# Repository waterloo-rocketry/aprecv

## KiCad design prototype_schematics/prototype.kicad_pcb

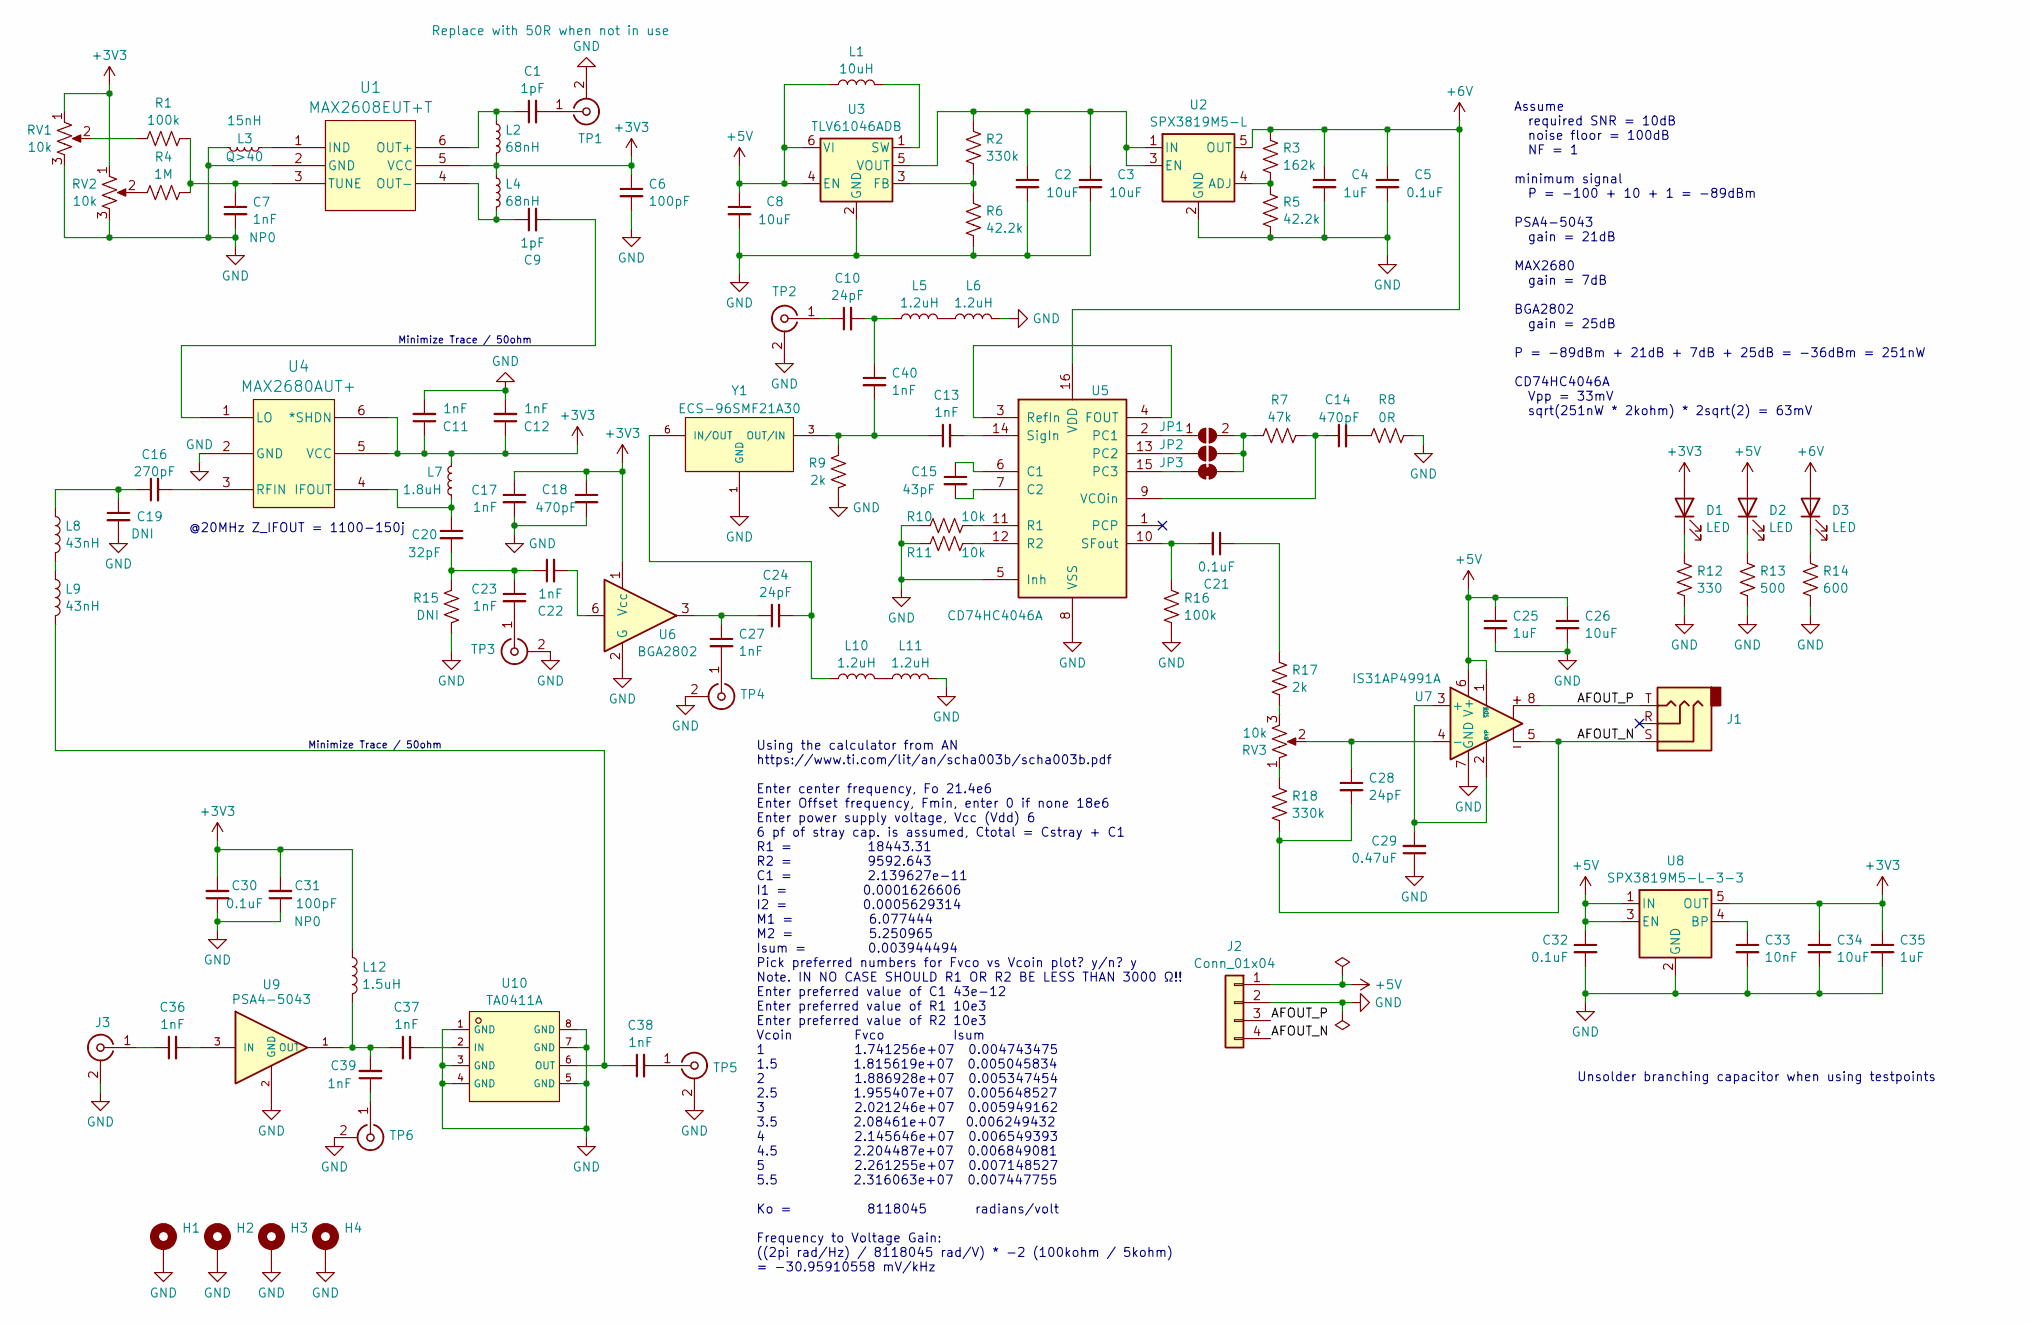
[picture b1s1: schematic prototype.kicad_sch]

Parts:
C1, C9: 1pF; C_0603_1608Metric_Pad1.08x0.95mm_HandSolder; Digikey 490-16342-1-ND
C2, C3, C8, C26, C34: 10uF; C_0805_2012Metric_Pad1.18x1.45mm_HandSolder
C4, C25, C35: 1uF; C_0805_2012Metric_Pad1.18x1.45mm_HandSolder
C5, C21, C30, C32: 0.1uF; C_0805_2012Metric_Pad1.18x1.45mm_HandSolder
C6, C31: 100pF; C_0603_1608Metric_Pad1.08x0.95mm_HandSolder; Digikey 720-1649-1-ND
C7, C11, C12, C13, C17, C22, C23, C27, C36, C37, C38, C39, C40: 1nF; C_0603_1608Metric_Pad1.08x0.95mm_HandSolder; Digikey 4713-GMC10CG102F50NTCT-ND
C10, C24, C28: 24pF; C_0603_1608Metric_Pad1.08x0.95mm_HandSolder; Digikey 13-CC0603FRNPO9BN240CT-ND
C14, C18: 470pF; C_0603_1608Metric_Pad1.08x0.95mm_HandSolder; Digikey 399-C0603C471F8HAC7867CT-ND
C15: 43pF; C_0603_1608Metric_Pad1.08x0.95mm_HandSolder; Digikey 490-GCM1885C2A430FA16DCT-ND
C16: 270pF; C_0603_1608Metric_Pad1.08x0.95mm_HandSolder; Digikey 490-16410-1-ND
C19: DNI; C_0603_1608Metric_Pad1.08x0.95mm_HandSolder
C20: 32pF; C_0603_1608Metric_Pad1.08x0.95mm_HandSolder; Digikey 478-06031A320FAT2ACT-ND
C29: 0.47uF; C_0805_2012Metric_Pad1.18x1.45mm_HandSolder; Digikey 1276-2082-1-ND
C33: 10nF; C_0805_2012Metric_Pad1.18x1.45mm_HandSolder; Digikey 490-4781-1-ND
D1, D2, D3: LED; LED_1206_3216Metric_Pad1.42x1.75mm_HandSolder
H1, H2, H3, H4: MountingHole_Pad; MountingHole_3.2mm_M3_Pad_TopBottom
J1: AudioJack3; CUI_SJ1-2503A; Digikey CP1-2503A-ND
J2: Conn_01x04; PinHeader_1x04_P2.54mm_Vertical
J3: Conn_Coaxial; SMA_Samtec_SMA-J-P-X-ST-EM1_EdgeMount; Digikey 931-1175-ND
JP1, JP3: SolderJumper_2_Open; SolderJumper-2_P1.3mm_Open_TrianglePad1.0x1.5mm
JP2: SolderJumper_2_Bridged; SolderJumper-2_P1.3mm_Open_TrianglePad1.0x1.5mm
L1: 10uH; L_0805_2012Metric_Pad1.15x1.40mm_HandSolder; Digikey 587-2045-1-ND
L2, L4: 68nH; L_0805_2012Metric_Pad1.15x1.40mm_HandSolder; Digikey 712-LRW0805WJ68NGG001ECT-ND
L3: 15nH; L_0603_1608Metric_Pad1.05x0.95mm_HandSolder; Digikey 490-1171-1-ND
L5, L6, L10, L11: 1.2uH; L_0805_2012Metric_Pad1.15x1.40mm_HandSolder; Digikey 2035-1186-1-ND
L7: 1.8uH; L_0805_2012Metric_Pad1.15x1.40mm_HandSolder; Digikey 445-MLF2012A1R8JT000CT-ND
L8, L9: 43nH; L_0603_1608Metric_Pad1.05x0.95mm_HandSolder; Digikey 490-6892-1-ND
L12: 1.5uH; L_0603_1608Metric_Pad1.05x0.95mm_HandSolder; Digikey 587-2898-1-ND
R1, R16: 100k; R_0805_2012Metric_Pad1.20x1.40mm_HandSolder
R2, R18: 330k; R_0805_2012Metric_Pad1.20x1.40mm_HandSolder; Digikey 311-330KCRCT-ND
R3: 162k; R_0805_2012Metric_Pad1.20x1.40mm_HandSolder; Digikey RMCF0805FT162KCT-ND
R4: 1M; R_0805_2012Metric_Pad1.20x1.40mm_HandSolder
R5, R6: 42.2k; R_0805_2012Metric_Pad1.20x1.40mm_HandSolder; Digikey 311-42.2KCRCT-ND
R7: 47k; R_0805_2012Metric_Pad1.20x1.40mm_HandSolder; Digikey 311-47.0KCRCT-ND
R8: 0R; R_0805_2012Metric_Pad1.20x1.40mm_HandSolder
R9, R17: 2k; R_0805_2012Metric_Pad1.20x1.40mm_HandSolder; Digikey RMCF0805FT2K00CT-ND
R10, R11: 10k; R_0805_2012Metric_Pad1.20x1.40mm_HandSolder
R12: 330; R_0805_2012Metric_Pad1.20x1.40mm_HandSolder
R13: 500; R_0805_2012Metric_Pad1.20x1.40mm_HandSolder
R14: 600; R_0805_2012Metric_Pad1.20x1.40mm_HandSolder
R15: DNI; R_0805_2012Metric_Pad1.20x1.40mm_HandSolder
RV1, RV2, RV3: 10k; TRIM_PT01-D120K2-B103; Digikey 2223-PT01-B120D-B103-ND
TP1, TP2, TP3, TP4, TP5, TP6: Conn_Coaxial; U.FL_Molex_MCRF_73412-0110_Vertical; Digikey 343-CONMHF1-SMD-TCT-ND
U1: MAX2608EUT+T; 21-0058I_MXM; Digikey MAX2608EUT+TCT-ND
U2: SPX3819M5-L; SOT-23-5; Digikey 1016-1871-1-ND
U3: TLV61046ADB; SOT-23-6; Digikey 296-47674-1-ND
U4: MAX2680AUT+; 21-0058I_MXM; Digikey 175-MAX2680AUT+TCT-ND
U5: CD74HC4046A; SOIC-16_3.9x9.9mm_P1.27mm; Digikey 296-9209-5-ND
U6: BGA2802; SOT-363_SC-70-6_Handsoldering; Digikey 568-14547-1-ND
U7: IS31AP4991A; SOP-8_3.76x4.96mm_P1.27mm; Digikey 2521-IS31AP4991A-GRLS2-TRCT-ND
U8: SPX3819M5-L-3-3; SOT-23-5; Digikey 1016-1873-1-ND
U9: PSA4-5043; Digikey 3157-PSA4-5043+CT-ND
U10: TA0411A; FILTER-SMD_8P-L5.0-W5.0-BL; LCSC C692400
Y1: ECS-96SMF21A30; XTAL_ECS-96SMF21A30; Digikey X717CT-ND

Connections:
+3V3: C6.1, C11.1, C12.1, C17.1, C18.1, C30.2, C31.2, C34.1, C35.1, D1.2 (A), L2.2, L4.1, L7.1, L12.1, RV1.1, RV2.1, U1.5 (VCC), U4.5 (VCC), U4.6 (*SHDN), U6.1 (Vcc), U8.5 (OUT)
+5V: C8.1, C25.1, C26.1, C32.1, D2.2 (A), J2.1, L1.1, U3.4 (EN), U3.6 (VI), U7.1 (~SDB), U7.6 (V+), U8.1 (IN), U8.3 (EN)
+6V: C4.1, C5.1, D3.2 (A), R3.1, U2.5 (OUT), U5.16 (VDD)
/AFOUT_N: C28.2, J1.S, J2.4, R18.2, U7.5
/AFOUT_P: J1.T, J2.3, U7.8
GND: C2.2, C3.2, C4.2, C5.2, C6.2, C7.2, C8.2, C11.2, C12.2, C17.2, C18.2, C19.2, C25.2, C26.2, C29.1, C30.1, C31.1, C32.2, C33.2, C34.2, C35.2, H1.1, H2.1, H3.1, H4.1, J2.2, J3.2 (Ext), L3.2, L6.2, L11.2, R5.2, R6.2, R8.2, R9.2, R10.1, R11.1, R12.2, R13.2, R14.2, R15.2, R16.2, RV1.3, RV2.3, TP1.2 (Ext), TP2.2 (Ext), TP3.2 (Ext), TP4.2 (Ext), TP5.2 (Ext), TP6.2 (Ext), U1.2 (GND), U2.2 (GND), U3.2 (GND), U4.2 (GND), U5.5 (Inh), U5.8 (VSS), U6.2 (G), U6.4 (G), U6.5 (G), U7.7 (GND), U8.2 (GND), U9.2 (GND), U9.4 (GND), U10.1 (GND), U10.3 (GND), U10.4 (GND), U10.5 (GND), U10.7 (GND), U10.8 (GND), Y1.1 (GND), Y1.2 (GND), Y1.4 (GND), Y1.5 (GND)
unnamed: C10.2, C40.1, L5.1
unnamed: C14.2, R8.1
unnamed: C16.1, C19.1, L8.1
unnamed: C20.2, C22.1, C23.1, R15.1
unnamed: C21.1, R17.1
unnamed: C22.2, U6.6
unnamed: C24.1, C27.1, U6.3
unnamed: D1.1 (K), R12.1
unnamed: D2.1 (K), R13.1
unnamed: D3.1 (K), R14.1
unnamed: C36.1, J3.1 (In)
unnamed: JP1.1 (A), U5.2 (PC1)
unnamed: JP1.2 (B), JP2.2 (B), JP3.2 (B), R7.1
unnamed: JP2.1 (A), U5.13 (PC2)
unnamed: JP3.1 (A), U5.15 (PC3)
unnamed: L5.2, L6.1
unnamed: L8.2, L9.1
unnamed: L10.2, L11.1
unnamed: R1.1, RV1.2
unnamed: R4.1, RV2.2
unnamed: R17.2, RV3.3
unnamed: R18.1, RV3.1
unnamed: C1.2, TP1.1 (In)
unnamed: C10.1, TP2.1 (In)
unnamed: C23.2, TP3.1 (In)
unnamed: C27.2, TP4.1 (In)
unnamed: C38.2, TP5.1 (In)
unnamed: C39.1, TP6.1 (In)
unnamed: L3.1, U1.1 (IND)
unnamed: C1.1, L2.1, U1.6 (OUT+)
unnamed: C9.1, L4.2, U1.4 (OUT-)
unnamed: C7.1, R1.2, R4.2, U1.3 (TUNE)
unnamed: R3.2, R5.1, U2.4 (ADJ)
unnamed: C2.1, C3.1, R2.1, U2.1 (IN), U2.3 (EN), U3.5 (VOUT)
unnamed: R2.2, R6.1, U3.3 (FB)
unnamed: L1.2, U3.1 (SW)
unnamed: C20.1, L7.2, U4.4 (IFOUT)
unnamed: C9.2, U4.1 (LO)
unnamed: C16.2, U4.3 (RFIN)
unnamed: C15.1, U5.6 (C1)
unnamed: C15.2, U5.7 (C2)
unnamed: U5.3 (RefIn), U5.4 (FOUT)
unnamed: R10.2, U5.11 (R1)
unnamed: R11.2, U5.12 (R2)
unnamed: C21.2, R16.1, U5.10 (SFout)
unnamed: C13.2, U5.14 (SigIn)
unnamed: C14.1, R7.2, U5.9 (VCOin)
unnamed: C29.2, U7.2 (BYP), U7.3 (+)
unnamed: C28.1, RV3.2, U7.4 (-)
unnamed: C33.1, U8.4 (BP)
unnamed: C36.2, U9.3 (IN)
unnamed: C37.1, C39.2, L12.2, U9.1 (OUT)
unnamed: C37.2, U10.2 (IN)
unnamed: C38.1, L9.2, U10.6 (OUT)
unnamed: C24.2, L10.1, Y1.6 (IN/OUT)
unnamed: C13.1, C40.2, R9.1, Y1.3 (OUT/IN)

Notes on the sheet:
Using the calculator from AN https://www.ti.com/lit/an/scha003b/scha003b.pdf Enter center frequency, Fo 21.4e6 Enter Offset frequency, Fmin, enter 0 if none 18e6 Enter power supply voltage, Vcc (Vdd) 6 6 pf of stray cap. is assumed, Ctotal = Cstray + C1 R1 = 18443.31 R2 = 9592.643 C1 = 2.139627e-11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
Unsolder branching capacitor when using testpoints
Assume required SNR = 10dB noise floor = 100dB NF = 1 minimum signal P = -100 + 10 + 1 = -89dBm PSA4-5043 gain = 21dB MAX2680 gain = 7dB BGA2802 gain = 25dB P = -89dBm + 21dB + 7dB + 25dB = -36dBm = 251nW CD74HC4046A Vpp = 33mV sqrt(251nW * 2kohm) * 2sqrt(2) = 63mV
Minimize Trace / 50ohm
@20MHz Z_IFOUT = 1100-150j

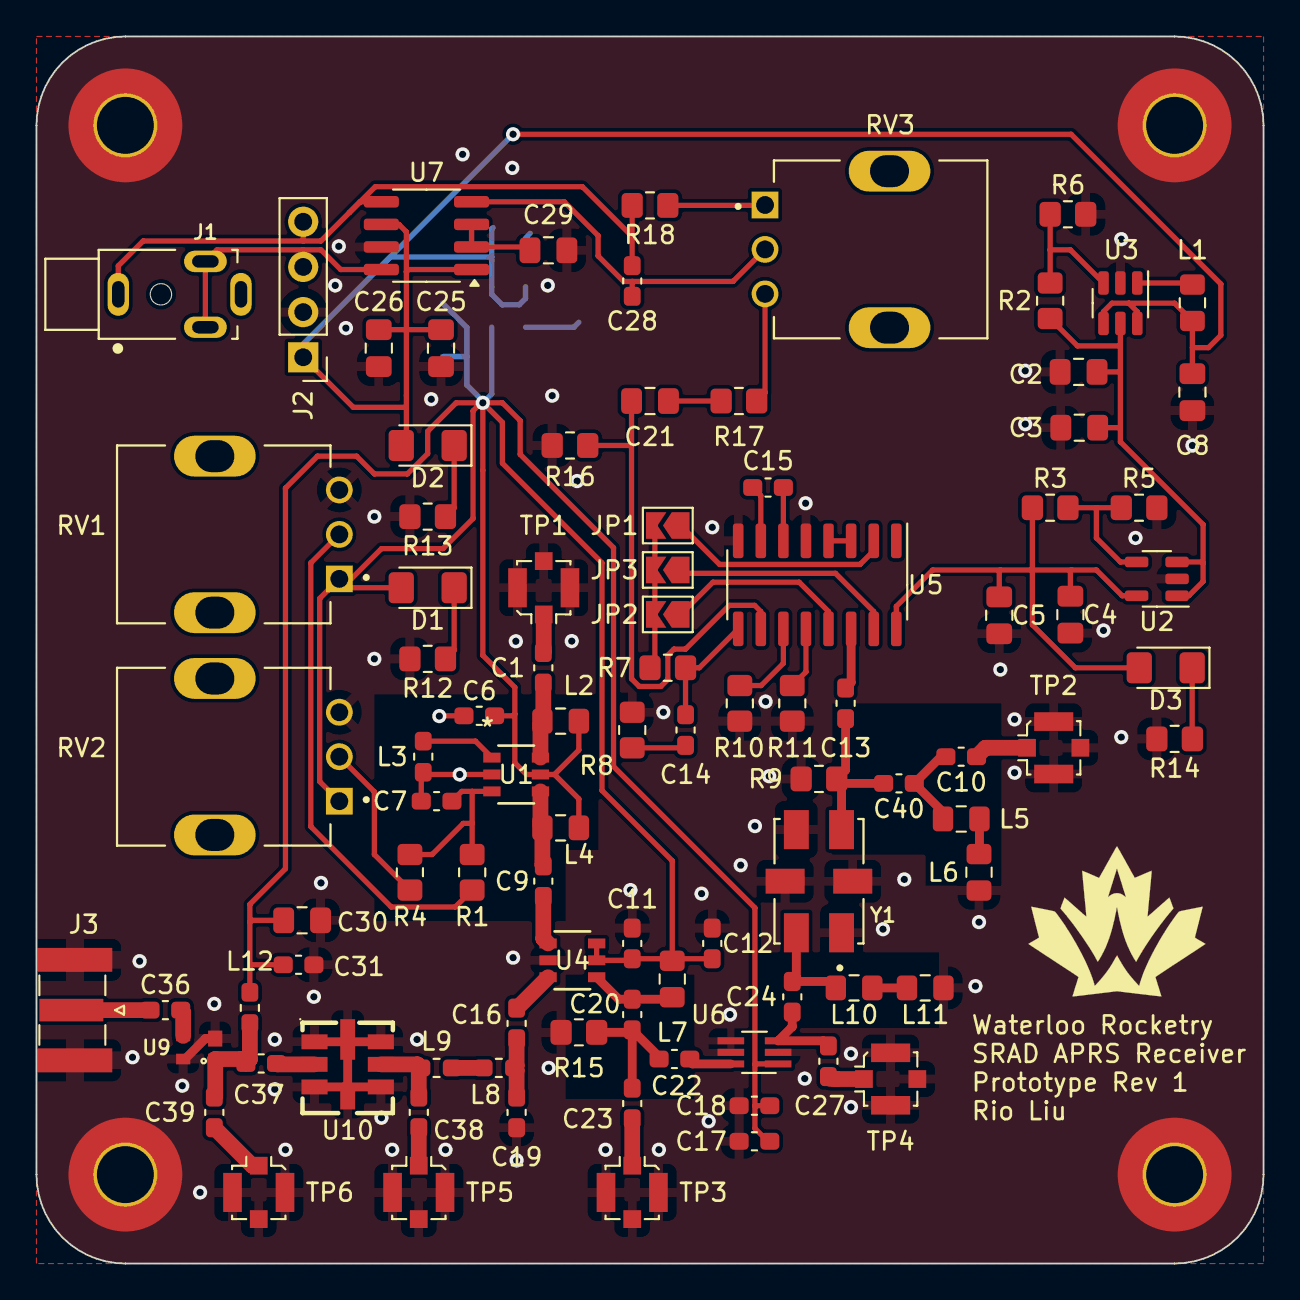
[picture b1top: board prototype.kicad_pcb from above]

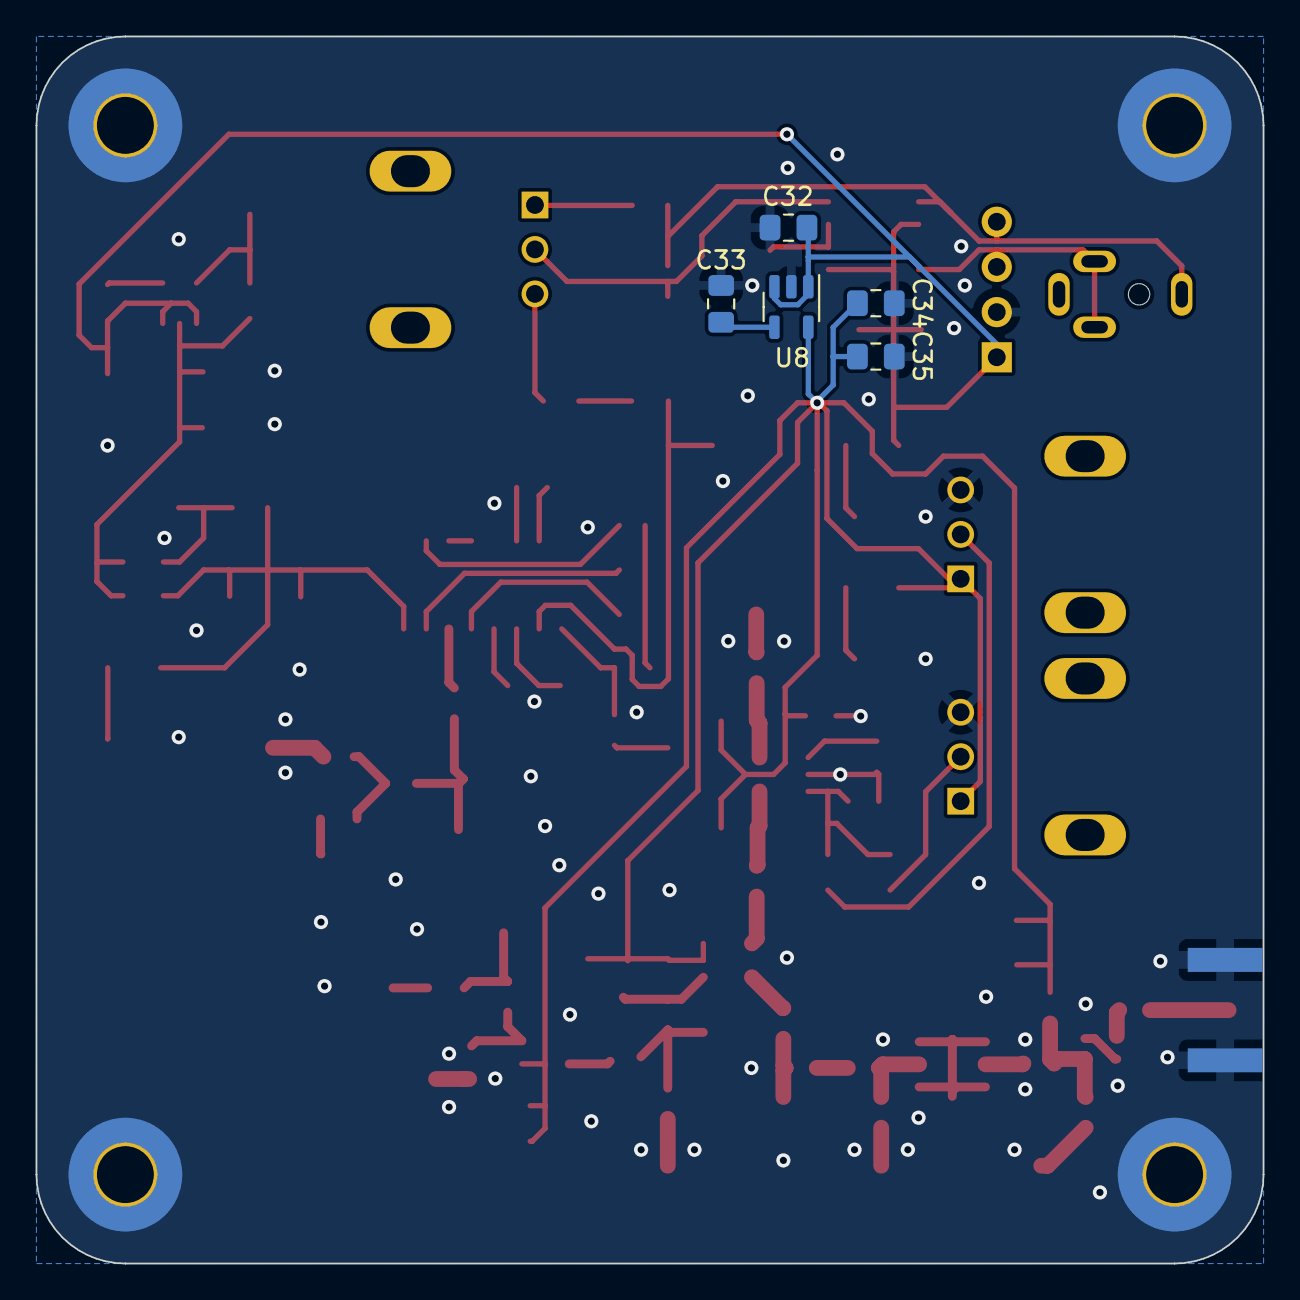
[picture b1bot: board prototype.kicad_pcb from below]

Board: 2 copper layers, 69.0 x 69.0 mm, 103 parts (5 on the bottom side), 62 nets.

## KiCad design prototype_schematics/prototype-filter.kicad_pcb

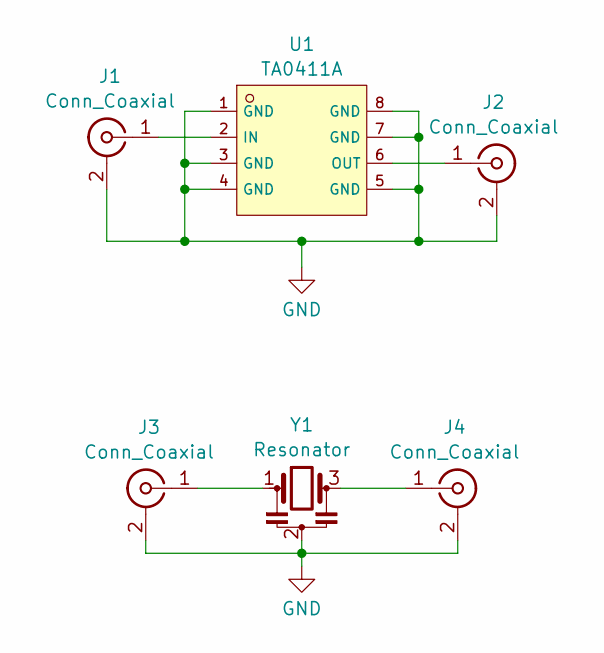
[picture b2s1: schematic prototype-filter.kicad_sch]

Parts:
J1, J2, J3, J4: Conn_Coaxial; SMB_Jack_Vertical
U1: TA0411A; FILTER-SMD_8P-L5.0-W5.0-BL; LCSC C692400
Y1: Resonator; CSTNE24M0VH3C000R0_MUR

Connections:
GND: J1.2 (Ext), J2.2 (Ext), J3.2 (Ext), J4.2 (Ext), U1.1 (GND), U1.3 (GND), U1.4 (GND), U1.5 (GND), U1.7 (GND), U1.8 (GND), Y1.2
unnamed: J1.1 (In), U1.2 (IN)
unnamed: J2.1 (In), U1.6 (OUT)
unnamed: J3.1 (In), Y1.1
unnamed: J4.1 (In), Y1.3

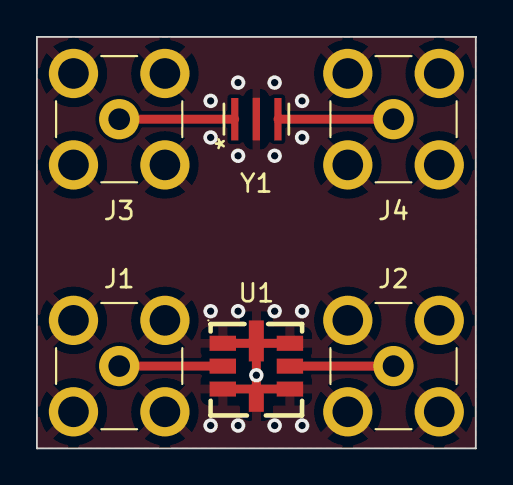
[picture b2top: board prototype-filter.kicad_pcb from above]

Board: 2 copper layers, 24.4 x 22.9 mm, 6 parts (0 on the bottom side), 5 nets.

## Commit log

2023-11-27 create a prototype pll schematics
2023-11-27 create cons multiplier in fpga and switch to sv
2023-12-05 update prototype schematics
2023-12-08 add IF synthesizer and update PLL + AF amp gains
2023-12-11 move prototype schematics to another branch
2023-12-11 add prototype schematics
2023-12-18 update schematics
2023-12-31 add if filter
2024-01-09 bump PLL to 20MHz and add a SAW filter
2024-01-15 add a prototype filter board
2024-01-15 update prototype filter board
2024-02-15 Add FPGA IC custom symbol
2024-03-21 Add afsk demodulation algo model
2024-03-21 Add matlab script for gen filter coeffs
2024-03-27 Initial FPGA schematics
2024-04-14 adding filters and amps
2024-04-19 Add decoupling capacitor and IO connectors
2024-04-19 match IF amplifier; switch to different LNA (wip)
2024-04-19 Add new SystemVerilog RTL simulation environment
2024-04-19 add testpoints
2024-04-19 add dedicated ldo for lna
2024-04-21 add switching regulator to get +6V
2024-04-21 add more testpoint
2024-04-21 update some cap and inductor values
2024-04-21 update pdf
2024-04-24 fix testpoint impedance matching; remove dedicated LDO
2024-05-01 add digikey parts and replace af amp
2024-05-03 add digikey part numbers
2024-05-05 add more digikey part numbers
2024-05-14 finish sourcing and footprints
2024-05-16 layout wip
2024-05-17 wip layout
2024-05-23 preliminary layout finished
2024-05-24 layout adjustment and edge cut
2024-05-31 wip routing
2024-06-02 finish routing
2024-06-06 add a few more gnd vias
2024-06-12 APRS analog prototype board (#1)
    * add prototype schematics
    * update schematics
    * add if filter
    * bump PLL to 20MHz and add a SAW filter
    * add a prototype filter board
    * update prototype filter board
2024-10-16 fig IS31AP4991A footprint; update default pll solder joint
